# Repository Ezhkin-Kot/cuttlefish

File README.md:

# Cuttlefish

<table>
  <tr>
    <td width="35%" valign="top">
      
    </td>
    <td width="65%" valign="top">
      <p>
        <strong>Cuttlefish</strong> is an autonomous RC car platform built around an Orange Pi 3B single-board computer and an Arduino Nano microcontroller.
      </p>
      <p>
        The vehicle uses a camera as its primary sensor. Video is processed by an autopilot running on the Orange Pi, which generates steering and motor commands.
        An Arduino Nano handles low-level motor and servo control.
      </p>
      <p>
        The project combines custom 3D-printed mechanics, dedicated power and interconnection electronics, embedded firmware, and computer vision software.
      </p>
    </td>
  </tr>
</table>

<br clear="left" />

## Features

- Custom 3D-printed chassis with Ackermann steering geometry.
- Rear-wheel drive with a 12 V geared DC motor.
- Arduino Nano for low-level hardware control.
- Orange Pi 3B for video processing and autonomous navigation.
- USB UVC camera with MJPEG output.
- Two autopilot deployment modes (**TODO**):
  - **Onboard:** all computations run directly on the Orange Pi.
  - **Remote:** video is streamed to an external computer, which runs the autopilot and sends control commands back.
- Modular architecture designed to support different autonomous driving algorithms (**TODO**).

## Project Status

| Component                  | Status         |
| -------------------------- | -------------- |
| Mechanical platform        | Complete       |
| Power electronics          | Complete       |
| Interconnection PCB        | Complete       |
| Arduino firmware           | Prototype      |
| Camera and video streaming | Complete       |
| Orange Pi control software | In development |
| Autonomous navigation      | Planned        |

## System Architecture

The system is divided into two main computing units, each responsible for a separate layer of control.

```text
                  Orange Pi 3B
              ┌───────────────────┐
 Camera ─────►│ Video acquisition │
              │        ↓          │
              │ Scene processing  │
              │        ↓          │
              │     Autopilot     │
              │        ↓          │
              │ Control commands  │
              └─────────┬─────────┘
                        │ USB Serial
                        │ 115200 baud
                        ▼
                  Arduino Nano
              ┌───────────────────┐
              │ Command parsing   │
              │ Motor PWM control │
              │ Servo control     │
              └────┬─────────┬────┘
                   │         │
               TB6612FNG   MG90S
                   │         │
                DC motor  Steering
```

### Orange Pi 3B

The SBC handles high-level operations:

- Camera capture and video processing.
- Autonomous navigation.
- Control algorithm execution.
- Communication with the Arduino.
- Video streaming and remote control interfaces.

### Arduino Nano

The MCU handles low-level hardware operations:

- DC motor speed and direction control.
- Steering servo control.
- Receiving and parsing commands over Serial.

This separation allows autonomous driving algorithms to be developed independently of the low-level hardware implementation.

## Hardware

### Components

| Component                   | Description                                     |
| --------------------------- | ----------------------------------------------- |
| Chassis                     | Custom 3D-printed platform                      |
| Drive motor                 | 12 V geared DC motor                            |
| Steering                    | MG90S servo with Ackermann steering linkage     |
| Motor driver                | TB6612FNG                                       |
| Microcontroller (MCU)       | Arduino Nano                                    |
| Single-board computer (SBC) | Orange Pi 3B (2 GB RAM)                         |
| Camera                      | OV2710 GXIVISION, 2 MP, 1080p, 30 FPS, 100° FOV |
| Battery                     | 3 × 18650 Li-ion cells (3S)                     |
| Main DC-DC converter        | MP1584, 12 V to 5 V, 3 A                        |
| SBC DC-DC converter         | XL4015E, 12 V to 5 V, 4 A                       |

### Power System

The vehicle is powered by a 3S 18650 Li-ion battery pack.

```text
              3S Battery Pack
                 (~11.1 V)
                     │
                Power Switch
                     │
        ┌────────────┼────────────┐
        │            │            │
  TB6612FNG VM     MP1584      XL4015E
        │            │            │
    DC Motor      5 V rail     5 V rail
                     │            │
               Arduino Nano    Orange Pi
               + TB6612FNG VCC
               + Servo
```

The two DC-DC converters provide separate 5 V power rails for the control electronics and the single-board computer.

The battery cells are removable and charged using an external charger.

**Battery protection is not yet implemented.** The current prototype does not include a BMS or automatic undervoltage cutoff.
Battery voltage must therefore be monitored manually. Avoid discharging individual cells below approximately 3.0 V.

### Interconnection PCB

The vehicle uses a dedicated interconnection PCB as part of its power and electronics assembly.
Two 470 µF / 16 V electrolytic capacitors are mounted on the board to help stabilize the power supply.

The KiCad project is available in [`hardware/schemas/`](hardware/schemas/). It includes:

- `cuttlefish-carrier.kicad_sch` — schematic.
- `cuttlefish-carrier.kicad_pcb` — PCB layout.
- `gerber/` — manufacturing files.
- `cuttlefish-carrier.csv`, `cuttlefish-carrier.xlsx` — bills of materials.
- `cuttlefish-carrier-all-pos.csv` — component placement data.

### Arduino Pinout

| Arduino Pin | Function                            |
| ----------- | ----------------------------------- |
| D9          | Steering servo signal               |
| D3 (PWM)    | TB6612FNG PWMA                      |
| D2          | TB6612FNG AIN1                      |
| D4          | TB6612FNG AIN2                      |
| D5          | TB6612FNG STBY                      |
| USB         | Serial communication with Orange Pi |

The current implementation uses USB Serial communication at 115200 baud. Hardware UART communication is a possible future alternative.

**Note:** Arduino Nano uses 5 V logic, while Orange Pi GPIO uses 3.3 V logic. Direct UART connections require appropriate logic-level conversion.

## Mechanical Design

The chassis is designed in Fusion 360 and manufactured using 3D printing.

Source files and printable models are available in<br/>[`hardware/3d-models/`](hardware/3d-models/):

- `cuttlefish.f3d` — parametric Fusion 360 model.
- `cuttlefish.stl` — printable chassis model.

## Software

The software is split between the Arduino firmware and the Orange Pi application.

### Arduino Firmware

Source code: [`mcu-firmware/`](mcu-firmware/)

The current firmware implements basic manual control over Serial communication.

| Command   | Action                                |
| --------- | ------------------------------------- |
| `w`       | Move forward                          |
| `s`       | Move backward                         |
| `x`       | Stop the motor                        |
| `a` / `d` | Start steering left / right           |
| `e` / `q` | Stop steering left / right            |
| `c`       | Immediately return steering to center |

Current steering parameters:

- Servo center: 90°.
- Maximum steering offset: ±40°.
- Steering movement: 0.8° every 15 ms.
- Default motor PWM: 200 / 255.

The current firmware is a prototype intended for manual control.
A more advanced command protocol with numerical steering and motor speed values, telemetry, and a communication watchdog is planned.

### Orange Pi Software

The Orange Pi application is planned in **Rust** and will serve as the main interface between the camera, autopilot, and microcontroller.

Planned functionality:

- Camera capture through V4L2.
- Serial communication with Arduino.
- Pluggable autopilot implementations.
- Local and remote autonomous driving modes.
- Remote video streaming and manual control.
- Recording camera frames and corresponding control commands for dataset collection.

The target operating system is **Armbian (Debian 13)**.

### Camera and Video Streaming

The camera is an OV2710-based USB UVC device that provides MJPEG video without requiring software-side encoding.

A working video streaming prototype is available in [`software/cam-test/`](software/cam-test/).

It is implemented in Rust using:

- `axum` for the HTTP server and WebSocket communication.
- `v4l` for camera access through V4L2.

The application captures MJPEG frames and forwards them to connected clients over WebSocket.
A browser-based interface displays the video stream along with FPS and bandwidth statistics.

**Supported camera modes:**

| Resolution  | Frame rate |
| ----------- | ---------- |
| 1920 × 1080 | 30 FPS     |
| 1280 × 1024 | 30 FPS     |
| 1280 × 960  | 30 FPS     |
| 1280 × 720  | 30 FPS     |
| 1024 × 768  | 30 FPS     |
| 800 × 600   | 30 FPS     |
| 640 × 480   | 30 FPS     |
| 352 × 288   | 30 FPS     |
| 320 × 240   | 30 FPS     |

**Building and running:**

Install the required dependencies:

```bash
sudo apt install -y build-essential libclang-dev clang v4l-utils
```

Build the application:

```bash
cd cam-test
cargo build --release
```

Run the video server:

```bash
./target/release/cam-test /dev/video4 1280 720 30 8080
```

Arguments:

```text
[device] [width] [height] [fps] [port]
```

Open the following address in a browser:

```text
http://<orange-pi-ip>:8080/
```

The camera exposes separate video and metadata device nodes. Their `/dev/videoN` numbers may change between system boots.
For reliable device selection, use a persistent path from `/dev/v4l/by-id/`.

**Build note:** `libclang-dev` is required by `v4l2-sys-mit` for bindgen. The application must be built in a Linux environment with the required V4L2 headers.

## Autonomous Navigation

The project is intended to support multiple autonomous driving approaches through a modular autopilot interface.

Two approaches are currently considered:

### Classical Computer Vision

An OpenCV-based pipeline without machine learning:

- Image preprocessing.
- Road and lane detection using color segmentation and edge detection.
- Geometric analysis and perspective transformations.
- Steering angle estimation.
- PID-based control.

### Neural Network-Based Navigation

A neural network that predicts steering and potentially motor speed directly from camera frames.

One possible approach is **behavioral cloning**, where the model is trained using camera footage paired with control commands recorded during manual driving.

This requires a dataset collection pipeline and an appropriate training workflow.

### Deployment Modes

Both approaches are intended to support two execution modes.

| Aspect              | Onboard                        | Remote                                  |
| ------------------- | ------------------------------ | --------------------------------------- |
| Computation         | Orange Pi 3B                   | External computer                       |
| Video processing    | Local                          | Remote                                  |
| Network dependency  | None                           | Wi-Fi                                   |
| Latency             | Lower                          | Includes network and streaming overhead |
| Computing resources | Limited by RK3566 and 2 GB RAM | Depends on external hardware            |

The remote mode uses WebSocket communication to transmit camera frames to an external computer and receive control commands in return.

The Orange Pi acts as a bridge between the network and the Arduino.

### Hardware Acceleration

The Orange Pi 3B is based on the Rockchip RK3566 and provides an NPU rated at approximately 0.8 TOPS.

Hardware acceleration through the RKNN toolkit is a potential option for neural network inference. Integration with the Rust application is yet to be investigated.

## Repository Structure

```text
cuttlefish/
├── hardware/
│   ├── 3d-models/   # Fusion 360 source and printable models
│   └── schemas/     # KiCad schematics, PCB, Gerber files and BOM
├── mcu-firmware/    # Arduino Nano firmware
├── README.md        # Project documentation
└── software/
    └── cam-test/    # Rust-based camera streaming prototype
```

Additional software components will be added as development progresses.

## Future Development

The following improvements are planned:

- [ ] Implement the Orange Pi control application.
- [ ] Develop a unified numerical Serial command protocol.
- [ ] Add a communication watchdog and fail-safe motor stop.
- [ ] Implement autonomous navigation algorithms.
- [ ] Collect training data for neural network-based navigation.
- [ ] Add battery voltage monitoring and undervoltage protection.
- [ ] Evaluate the accuracy of camera-only navigation.
- [ ] Measure video streaming latency and system performance.
- [ ] Investigate RKNN-based neural network acceleration.
- [ ] Improve calibration and repeatability across multiple vehicles.

The platform is also intended to serve as a reproducible hardware base for educational events and robotics hackathons.

## License

Cuttlefish consists of hardware and software components distributed under separate open-source licenses.

| Component                      | License        |
| ------------------------------ | -------------- |
| Hardware designs (`hardware/`) | CERN-OHL-S-2.0 |
| MCU firmware (`mcu-firmware/`) | GPL-3.0-only   |
| Software (`software/`)         | GPL-3.0-only   |

See the respective `LICENSE` files in each directory
for the full license texts.

Third-party components remain under their respective licenses.

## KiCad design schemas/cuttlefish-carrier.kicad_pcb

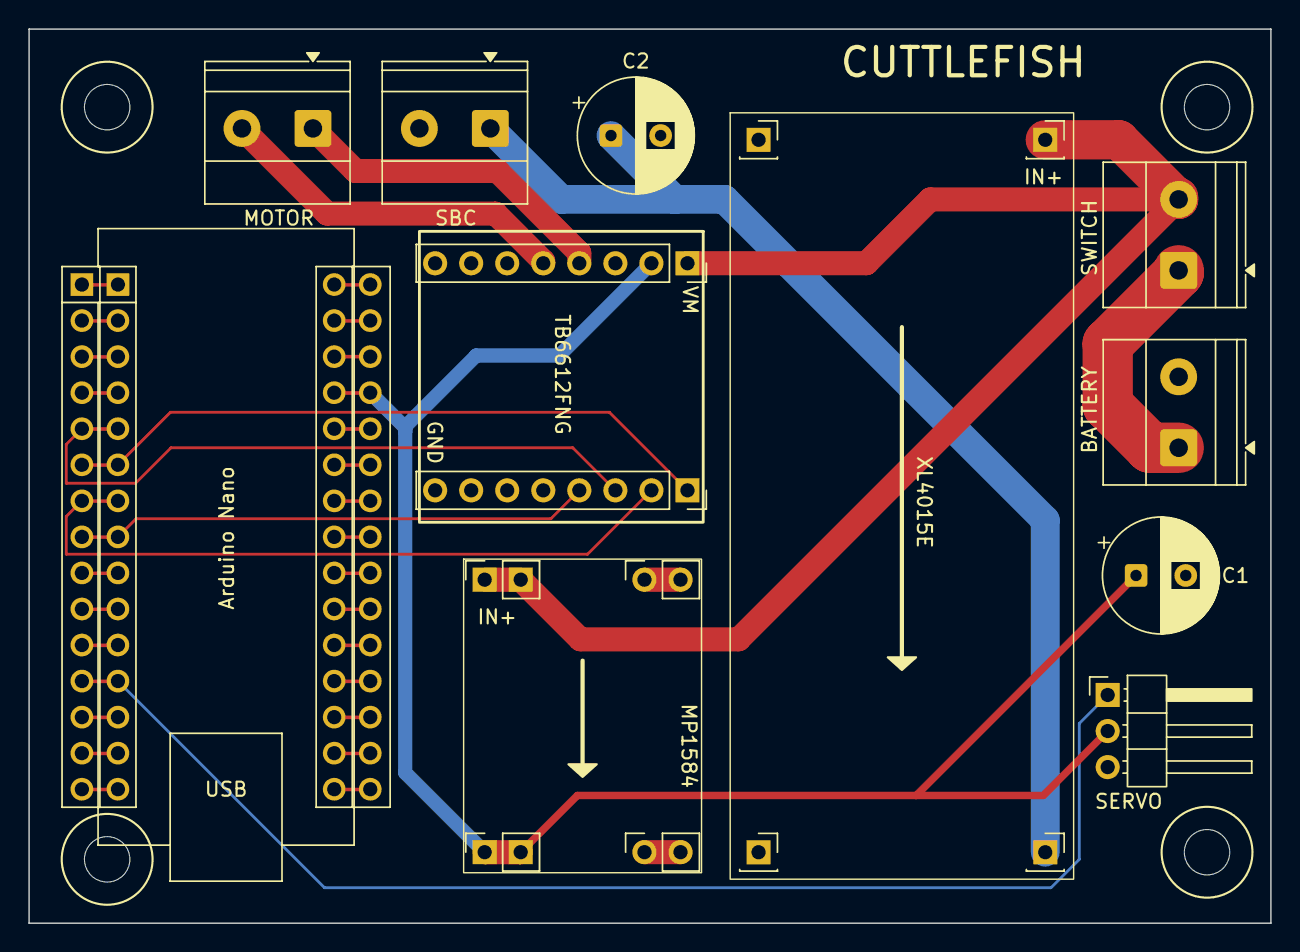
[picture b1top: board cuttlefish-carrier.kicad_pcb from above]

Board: 2 copper layers, 87.5 x 63.0 mm, 11 parts (0 on the bottom side), 12 nets.

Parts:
Arduino Nano1: Arduino_Nano_v3.x; Arduino_Nano_Socket_2x15
BATTERY1: Battery_Socket; TerminalBlock_Phoenix_MKDS-1,5-2_1x02_P5.00mm_Horizontal
C1, C2: 470uF_16V; CP_Radial_D8.0mm_P3.50mm
MOTOR1: Motor_Socket; TerminalBlock_Phoenix_MKDS-1,5-2_1x02_P5.00mm_Horizontal
MP1584: MP1584_PinSocket
SBC1: SBC_Socket; TerminalBlock_Phoenix_MKDS-1,5-2_1x02_P5.00mm_Horizontal
SRV1: Servo_Socket; PinHeader_1x03_P2.54mm_Horizontal
SWITCH1: SW_SPST; TerminalBlock_Phoenix_MKDS-1,5-2_1x02_P5.00mm_Horizontal
TB6612FNG1: TB6612FNG_PinSocket
XL4015E1: XL4015E_PinSocket

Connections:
GND: Arduino Nano1.4 (GND), Arduino Nano1.29 (GND), BATTERY1.2, C1.2, C2.2, MP1584.2 (IN-), MP1584.4 (OUT-), SBC1.2, SRV1.3, TB6612FNG1.3 (GND), TB6612FNG1.8 (GND), TB6612FNG1.16 (GND), XL4015E1.2 (IN-), XL4015E1.4 (OUT-)
unnamed: Arduino Nano1.27 (+5V), C1.1, MP1584.3 (OUT+), SRV1.2, TB6612FNG1.2 (VCC)
unnamed: Arduino Nano1.5 (D2), TB6612FNG1.11 (AIN1)
unnamed: Arduino Nano1.6 (D3), TB6612FNG1.9 (PWMA)
unnamed: Arduino Nano1.7 (D4), TB6612FNG1.10 (AIN2)
unnamed: Arduino Nano1.8 (D5), TB6612FNG1.12 (STBY)
unnamed: Arduino Nano1.12 (D9), SRV1.1
unnamed: BATTERY1.1, SWITCH1.1 (A)
unnamed: MOTOR1.1, TB6612FNG1.4 (AO1)
unnamed: MOTOR1.2, TB6612FNG1.5 (AO2)
unnamed: MP1584.1 (IN+), SWITCH1.2 (B), TB6612FNG1.1 (VM), XL4015E1.1 (IN+)
unnamed: C2.1, SBC1.1, XL4015E1.3 (OUT+)
